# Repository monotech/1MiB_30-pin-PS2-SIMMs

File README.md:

1MiB 30-pin PS/2 Proprietary SIMMs
----------------------------------

These are standard 1MiB 30-pin SIMMs, that have the option to change them to PS/2 Proprietary type, as used in the motherboards of the Model 30-286 and Model 50, IBM Caching SCSI card, and IBM Multifunction Adapter for Model 30-286.

Documentation is on the rear silkscreen. Use a soldering iron and solder sucker to change between Standard mode and PS/2 mode.

These take nine rare TC511000BFTL chips. They are an odd package. The schematic will work for other modules; you'll just need to change the symbol to match whatever package you'll be using, and to hand-solder, you won't be able to use SOJ ICs in the usual arrangement; you'll need to make the modules larger.

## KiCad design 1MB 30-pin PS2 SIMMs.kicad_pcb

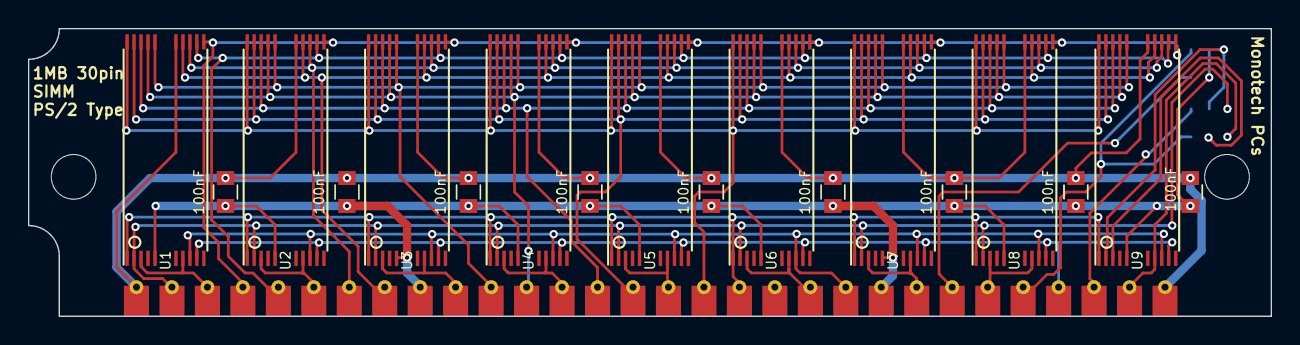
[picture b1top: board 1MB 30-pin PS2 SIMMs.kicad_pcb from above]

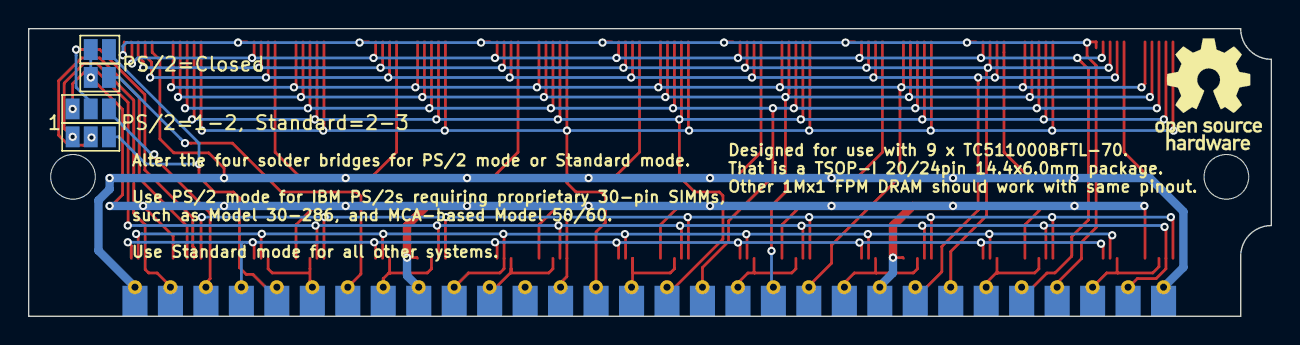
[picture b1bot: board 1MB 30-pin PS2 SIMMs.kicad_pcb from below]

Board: 2 copper layers, 89.0 x 20.6 mm, 23 parts (4 on the bottom side), 29 nets.

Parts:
C1, C2, C3, C4, C5, C6, C7, C8, C9: 100nF; C_0805
J5: 30pin_SIMM
JP1, JP2: PS/2=Closed; SolderJumper-2_P1.3mm_Open_Pad1.0x1.5mm
JP3, JP4: PS/2=1-2, Standard=2-3; SolderJumper-3_P1.3mm_Open_Pad1.0x1.5mm_NumberLabels
U1, U2, U3, U4, U5, U6, U7, U8, U9: 511000-TSOP; TSOP-I-20-24_14.4x6mm_Pitch0.5mm

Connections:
A0: J5.4, U1.13, U2.13, U3.13, U4.13, U5.13, U6.13, U7.13, U8.13, U9.13
A1: J5.5, U1.14, U2.14, U3.14, U4.14, U5.14, U6.14, U7.14, U8.14, U9.14
A2: J5.7, U1.15, U2.15, U3.15, U4.15, U5.15, U6.15, U7.15, U8.15, U9.15
A3: J5.8, U1.16, U2.16, U3.16, U4.16, U5.16, U6.16, U7.16, U8.16, U9.16
A4: J5.11, U1.20, U2.20, U3.20, U4.20, U5.20, U6.20, U7.20, U8.20, U9.20
A5: J5.12, U1.21, U2.21, U3.21, U4.21, U5.21, U6.21, U7.21, U8.21, U9.21
A6: J5.14, U1.22, U2.22, U3.22, U4.22, U5.22, U6.22, U7.22, U8.22, U9.22
A7: J5.15, U1.23, U2.23, U3.23, U4.23, U5.23, U6.23, U7.23, U8.23, U9.23
A8: J5.17, U1.24, U2.24, U3.24, U4.24, U5.24, U6.24, U7.24, U8.24, U9.24
A9: J5.18, U1.1, U2.1, U3.1, U4.1, U5.1, U6.1, U7.1, U8.1, U9.1
CAS: J5.2, JP4.1, U1.2, U2.2, U3.2, U4.2, U5.2, U6.2, U7.2, U8.2
CASP: J5.28, JP4.3
D0: J5.3, U1.3, U1.9
D1: J5.6, U2.3, U2.9
D2: J5.10, U3.3, U3.9
D3: J5.13, U4.3, U4.9
D4: J5.16, U5.3, U5.9
D5: J5.20, U6.3, U6.9
D6: J5.23, U7.3, U7.9
D7: J5.25, U8.3, U8.9
DP: J5.29, JP3.1, U9.9
GND: C1.2, C2.2, C3.2, C4.2, C5.2, C6.2, C7.2, C8.2, C9.2, J5.9, J5.22, JP1.1, JP2.1, U1.5, U2.5, U3.5, U4.5, U5.5, U6.5, U7.5, U8.5, U9.5
unnamed: JP3.2, U9.3
unnamed: JP4.2, U9.2
Pres1: J5.24, JP2.2
QP: J5.26, JP1.2, JP3.3
RAS: J5.27, U1.11, U2.11, U3.11, U4.11, U5.11, U6.11, U7.11, U8.11, U9.11
VCC: C1.1, C2.1, C3.1, C4.1, C5.1, C6.1, C7.1, C8.1, C9.1, J5.1, J5.30, U1.17, U2.17, U3.17, U4.17, U5.17, U6.17, U7.17, U8.17, U9.17
WR: J5.21, U1.10, U2.10, U3.10, U4.10, U5.10, U6.10, U7.10, U8.10, U9.10
